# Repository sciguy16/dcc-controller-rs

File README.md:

# dcc-controller-rs
Open source lightweight DCC controller with firmware written in Rust

Based on the STM32F103C8T6 "blue pill" board - specifically the C8 version
rather than the C6 because the former has 64k of flash, and the graphics
components push the binary size up to around 51k.

## Features
* Two control potentiometers to control two locomotives, with short-mode
addresses selected via dipswitches
* Potentiometers are centre-off; rotate left to drive the corresponding
locomotive in reverse, and right to drive it forwards
* LED for each channel to show when it is active
* On-off-on mini slide switch to select programming mode
  * programming mode disables all control functions and just sends out
DCC IDLE packets until the "program" button is pressed
  * Controller will then send out the programming sequence to program the
locomotive with the address set on the selected channel
* Current measurement and overcurrent shut-off
* Overcurrent alarm LED
* Screw terminals to connect power supply and track outputs
* Pure-Rust open source firmware based on dcc-rs
* Open source hardware

## Installation
Ensure that the `thumbv7m-none-eabi` target and the `probe-run` tool have
been installed and then `cargo run --release` will automatically flash the
compiled firmware onto the device.

```bash
rustup target add thumbv7m-none-eabi
cargo install probe-run
cargo run --release
DEFMT_LOG=off cargo run --release # Disable defmt logging
```

# License
Source code for the software components is distributed under the terms
of the Mozilla Public License Version 2.0.

Design files for the hardware components are distributed under the terms
of the CERN Open Hardware Licence Version 2 - Weakly Reciprocal.

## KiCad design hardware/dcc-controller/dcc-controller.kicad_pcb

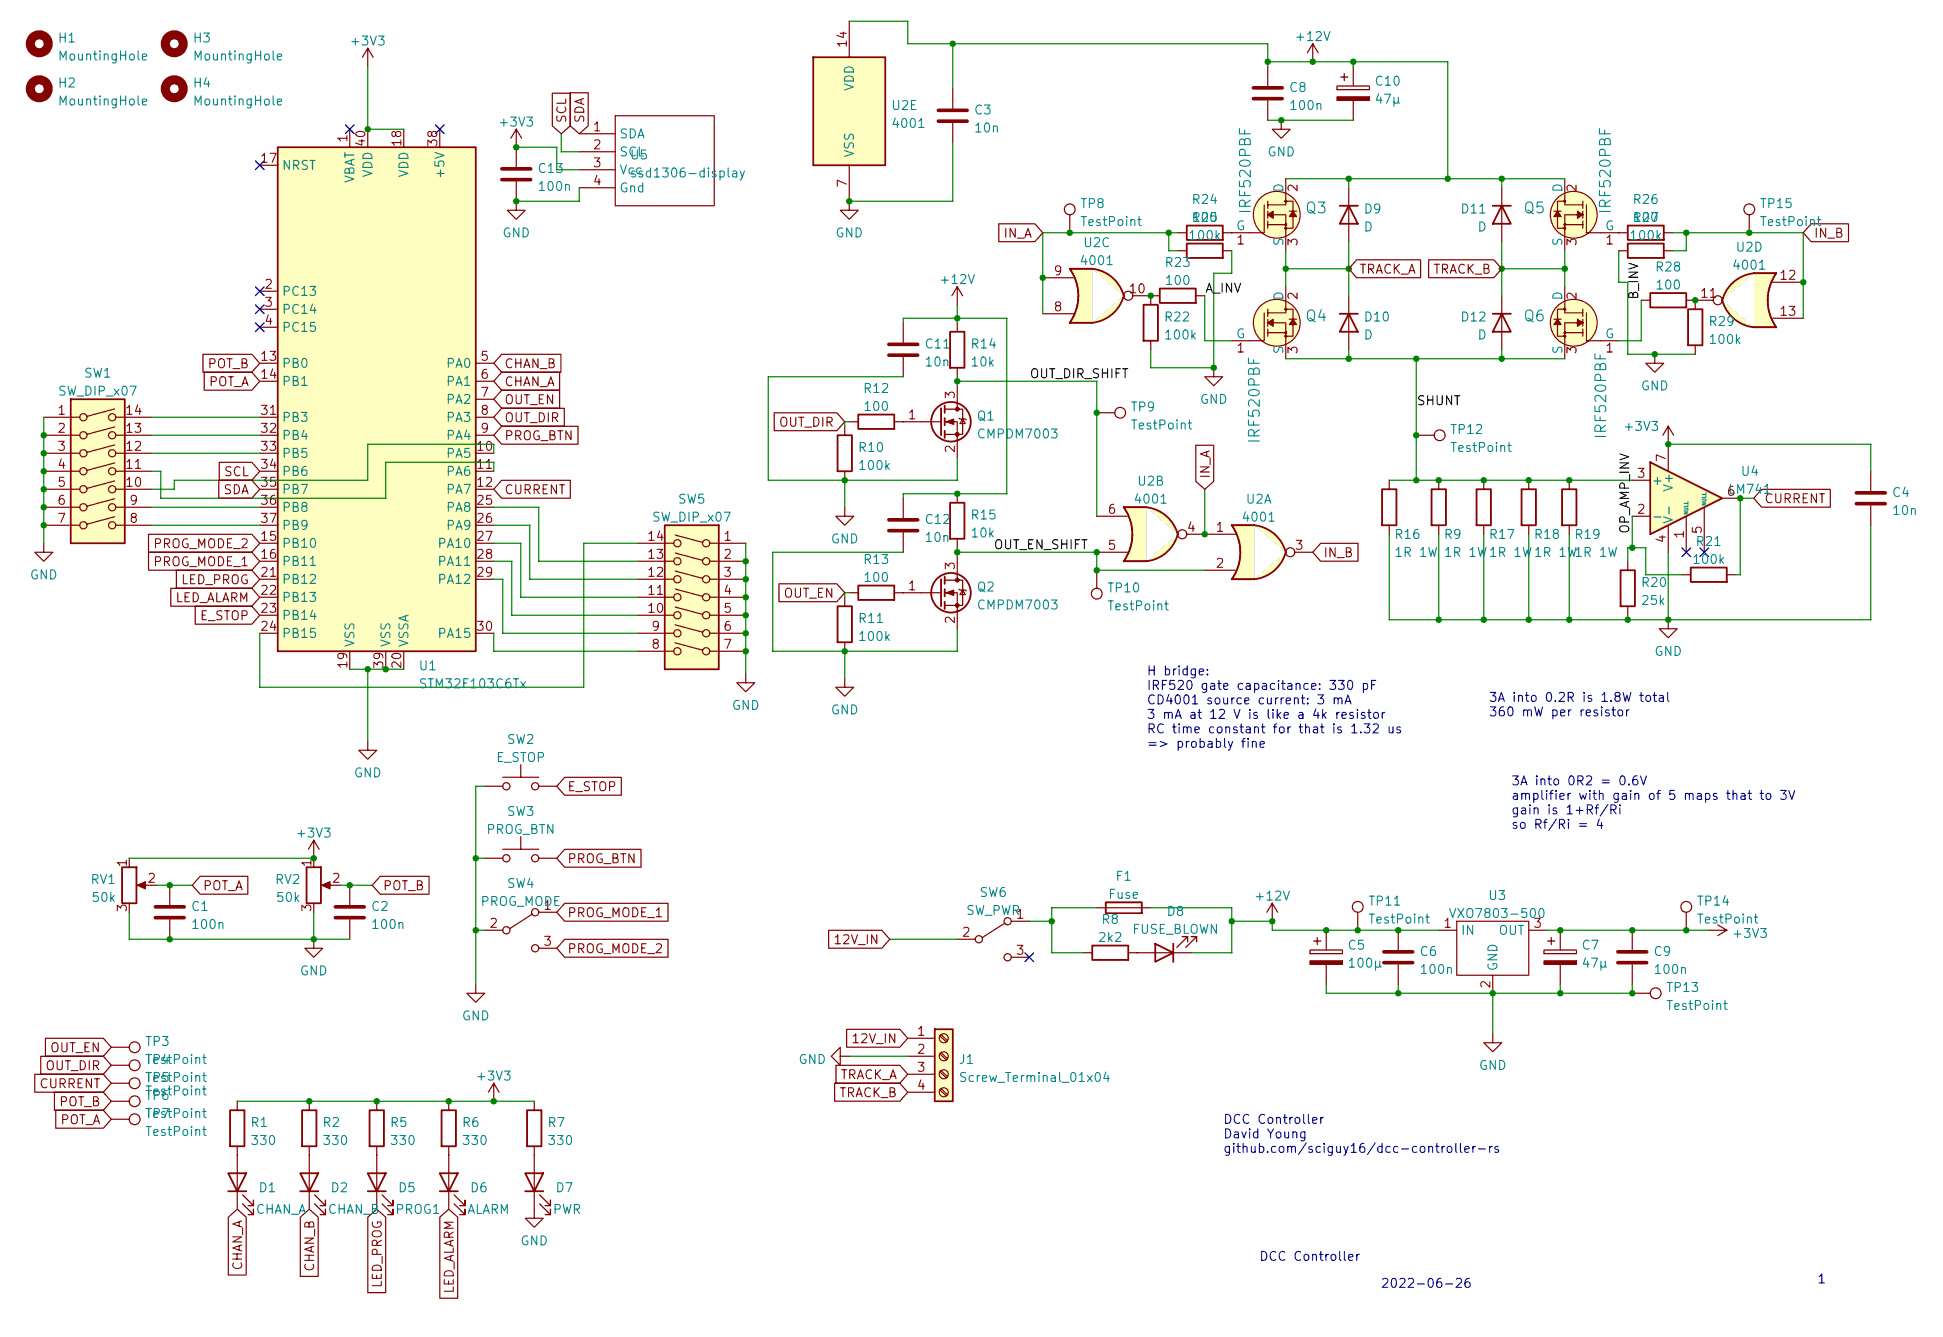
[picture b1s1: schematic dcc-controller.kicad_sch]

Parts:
C1, C2, C6, C8, C9, C13: 100n; C_0805_2012Metric
C3, C4, C11, C12: 10n; C_0805_2012Metric
C5: 100µ; CP_Radial_D5.0mm_P2.50mm
C7, C10: 47µ; CP_Radial_D5.0mm_P2.50mm
D1: CHAN_A; LED_0805_2012Metric
D2: CHAN_B; LED_0805_2012Metric
D5: PROG; LED_0805_2012Metric
D6: ALARM; LED_0805_2012Metric
D7: PWR; LED_0805_2012Metric
D8: FUSE_BLOWN; LED_0805_2012Metric
D9, D10, D11, D12: D; D_MELF
F1: Fuse; automotive-fuse-mount
H1, H2, H3, H4: MountingHole; MountingHole_3.2mm_M3
J1: Screw_Terminal_01x04; TerminalBlock_bornier-4_P5.08mm
Q1, Q2: CMPDM7003; SOT-23
Q3, Q4, Q5, Q6: IRF520PBF; TO-220F-3_Vertical; MPN IRF510PBF; Digi-Key_PN IRF510PBF-ND
R1, R2, R5, R6, R7: 330; R_0805_2012Metric
R8: 2k2; R_0805_2012Metric
R9, R16, R17, R18, R19: 1R 1W; R_Axial_DIN0207_L6.3mm_D2.5mm_P10.16mm_Horizontal
R10, R11, R21, R22, R25, R27, R29: 100k; R_0805_2012Metric
R12, R13, R23, R24, R26, R28: 100; R_0805_2012Metric
R14, R15: 10k; R_0805_2012Metric
R20: 25k; R_0805_2012Metric
RV1, RV2: 50k; Potentiometer_Bourns_PTV09A-1_Single_Vertical
SW1, SW5: SW_DIP_x07; DIP-14_W7.62mm_Socket
SW2: E_STOP; SW_PUSH_6mm_H5mm
SW3: PROG_BTN; SW_PUSH_6mm_H5mm
SW4: PROG_MODE; dp3t
SW6: SW_PWR; spdt-slide-switch
TP3, TP4, TP5, TP6, TP7, TP8, TP9, TP10, TP11, TP12, TP13, TP14, TP15: TestPoint; TestPoint_THTPad_D2.0mm_Drill1.0mm
U1: STM32F103C6Tx; stm32-blue-pill
U2: 4001; SOIC-14_3.9x8.7mm_P1.27mm
U3: VXO7803-500; TO-220-3_Vertical
U4: LM741; DIP-8_W7.62mm
U5: ssd1306-display

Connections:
12V_IN: J1.1, SW6.2 (B)
+3V3: C4.2, C7.1, C9.1, C13.1, R1.1, R2.1, R5.1, R6.1, R7.1, RV1.1, RV2.1, TP14.1, U1.18 (VDD), U1.40 (VDD), U3.3 (OUT), U4.7 (V+), U5.3 (Vcc)
+12V: C3.1, C5.1, C6.1, C8.2, C10.1, C11.1, C12.1, D8.1 (K), D9.1 (K), D11.1 (K), F1.2, Q3.2 (D), Q5.2 (D), R14.1, R15.1, TP11.1, U2.14 (VDD), U3.1 (IN)
/A_INV: Q4.1 (G), R23.2
/B_INV: Q6.1 (G), R28.1
/OP_AMP_INV: R20.1, R21.1, U4.2 (-)
/OUT_DIR_SHIFT: Q1.3 (D), R14.2, TP9.1, U2.6
/OUT_EN_SHIFT: Q2.3 (D), R15.2, TP10.1, U2.2, U2.5
/SHUNT: D10.2 (A), D12.2 (A), Q4.3 (S), Q6.3 (S), R9.1, R16.1, R17.1, R18.1, R19.1, TP12.1, U4.3 (+)
CHAN_A: D1.1 (K), U1.6 (PA1)
CHAN_B: D2.1 (K), U1.5 (PA0)
CURRENT: R21.2, TP5.1, U1.12 (PA7), U4.6
E_STOP: SW2.2, U1.23 (PB14)
GND: C1.2, C2.2, C3.2, C4.1, C5.2, C6.2, C7.2, C8.1, C9.2, C10.2, C11.2, C12.2, C13.2, D7.1 (K), J1.2, Q1.2 (S), Q2.2 (S), R9.2, R10.2, R11.2, R16.2, R17.2, R18.2, R19.2, R20.2, R22.2, R25.2, R27.1, R29.2, RV1.3, RV2.3, SW1.1, SW1.2, SW1.3, SW1.4, SW1.5, SW1.6, SW1.7, SW2.1, SW3.1, SW4.2 (B), SW5.1, SW5.2, SW5.3, SW5.4, SW5.5, SW5.6, SW5.7, TP13.1, U1.19 (VSS), U1.20 (VSSA), U1.39 (VSS), U2.7 (VSS), U3.2 (GND), U4.4 (V-), U5.4 (Gnd)
IN_A: R24.1, R25.1, TP8.1, U2.1, U2.4, U2.8, U2.9
IN_B: R26.2, R27.2, TP15.1, U2.3, U2.12, U2.13
LED_ALARM: D6.1 (K), U1.22 (PB13)
LED_PROG: D5.1 (K), U1.21 (PB12)
unnamed: D1.2 (A), R1.2
unnamed: D2.2 (A), R2.2
unnamed: D5.2 (A), R5.2
unnamed: D6.2 (A), R6.2
unnamed: D7.2 (A), R7.2
unnamed: D8.2 (A), R8.2
unnamed: F1.1, R8.1, SW6.1 (A)
unnamed: Q1.1 (G), R12.2
unnamed: Q2.1 (G), R13.2
unnamed: Q3.1 (G), R24.2
unnamed: Q5.1 (G), R26.1
unnamed: R22.1, R23.1, U2.10
unnamed: R28.2, R29.1, U2.11
unnamed: SW1.8, U1.37 (PB9)
unnamed: SW1.9, U1.36 (PB8)
unnamed: SW1.10, U1.10 (PA5)
unnamed: SW1.11, U1.11 (PA6)
unnamed: SW1.12, U1.33 (PB5)
unnamed: SW1.13, U1.32 (PB4)
unnamed: SW1.14, U1.31 (PB3)
unnamed: SW5.8, U1.30 (PA15)
unnamed: SW5.9, U1.29 (PA12)
unnamed: SW5.10, U1.28 (PA11)
unnamed: SW5.11, U1.27 (PA10)
unnamed: SW5.12, U1.26 (PA9)
unnamed: SW5.13, U1.25 (PA8)
unnamed: SW5.14, U1.24 (PB15)
OUT_DIR: R10.1, R12.1, TP4.1, U1.8 (PA3)
OUT_EN: R11.1, R13.1, TP3.1, U1.7 (PA2)
POT_A: C1.1, RV1.2, TP7.1, U1.14 (PB1)
POT_B: C2.1, RV2.2, TP6.1, U1.13 (PB0)
PROG_BTN: SW3.2, U1.9 (PA4)
PROG_MODE_1: SW4.1 (A), U1.16 (PB11)
PROG_MODE_2: SW4.3 (C), U1.15 (PB10)
SCL: U1.34 (PB6), U5.2 (SCL)
SDA: U1.35 (PB7), U5.1 (SDA)
TRACK_A: D9.2 (A), D10.1 (K), J1.3, Q3.3 (S), Q4.2 (D)
TRACK_B: D11.2 (A), D12.1 (K), J1.4, Q5.3 (S), Q6.2 (D)

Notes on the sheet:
DCC Controller
H bridge: IRF520 gate capacitance: 330 pF CD4001 source current: 3 mA 3 mA at 12 V is like a 4k resistor RC time constant for that is 1.32 us => probably fine
DCC Controller David Young github.com/sciguy16/dcc-controller-rs
2022-06-26
3A into 0.2R is 1.8W total 360 mW per resistor
3A into 0R2 = 0.6V amplifier with gain of 5 maps that to 3V gain is 1+Rf/Ri so Rf/Ri = 4

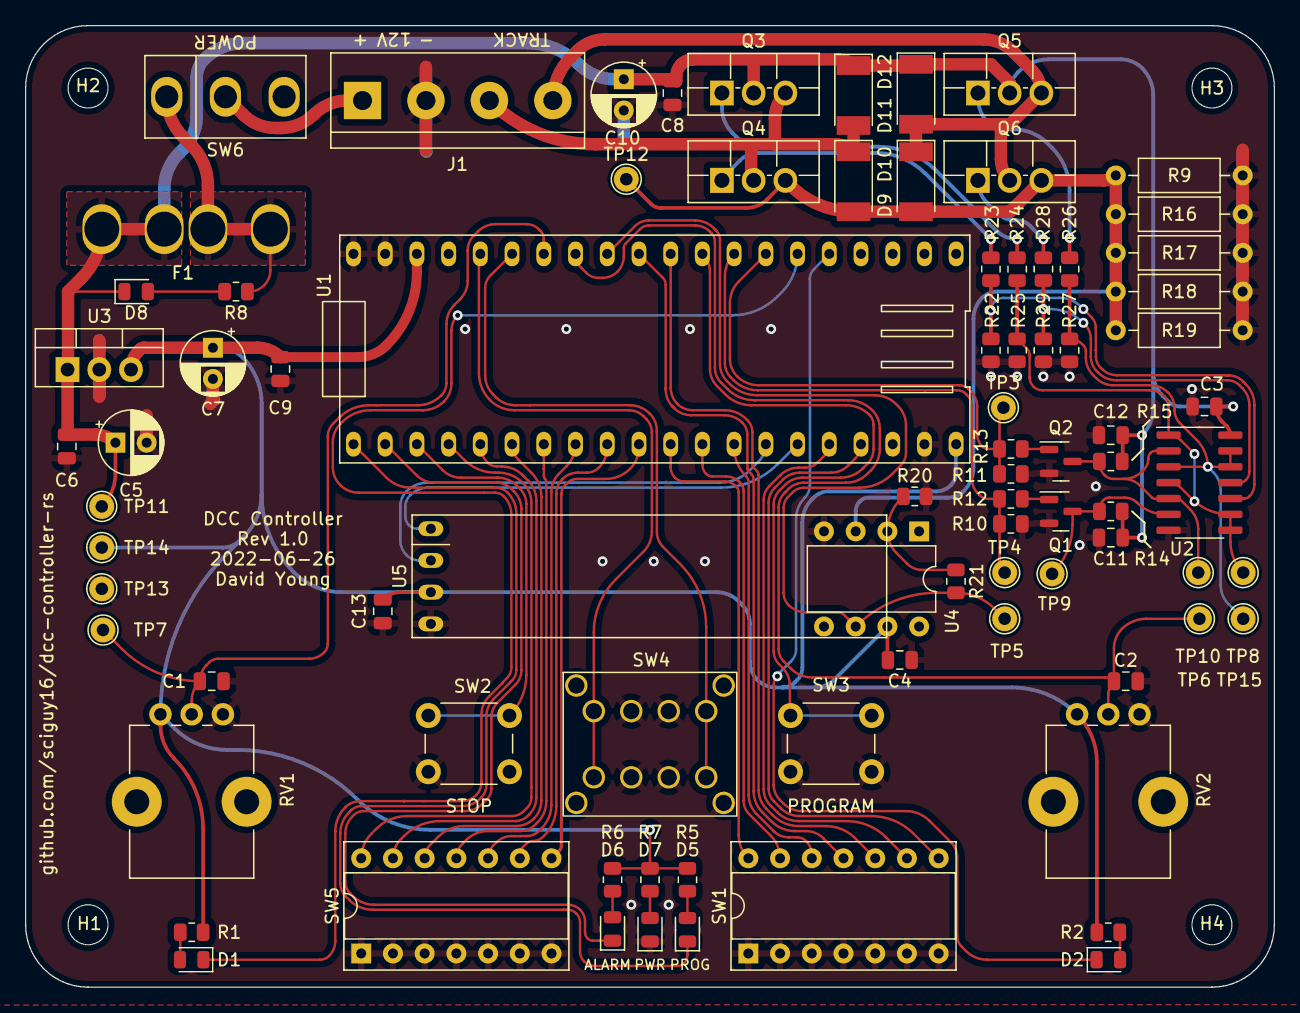
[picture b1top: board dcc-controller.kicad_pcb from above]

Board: 2 copper layers, 100.0 x 77.0 mm, 88 parts (0 on the bottom side), 56 nets.

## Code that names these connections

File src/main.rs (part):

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// file, you can obtain one at https://mozilla.org/MPL/2.0/.

// Pinout:
// POT_LEFT: PB0
// POT_RIGHT: PB1
// DIPSW_LEFT: PB15, PA8, PA9, PA10, PA11, PA12, PA15
// DIPSW_RIGHT: PB3, PB4, PB5, PA6, PA5, PB8, PB9
// SCL: PB6
// SDA: PB7
// LED_LEFT: PA1
// LED_RIGHT: PA0
// LED_PROG: PB12
// LED_ALARM: PB13
// BTN_STOP: PB14
// BTN_PROG: PA4
// SW_PROG_LEFT: PB10
// SW_PROG_RIGHT: PB11
// OUT_EN: PA2
// OUT_DIR: PA3
// CURRENT_SENSE: PA7

#![no_main]
#![no_std]
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}

// A type definition for the GPIO pin to be used for our LED
type DccDirPin = gpioa::PA3<Output<PushPull>>;

// Make DCC thingy globally available
static G_DCC: Mutex<RefCell<Option<DccInterruptHandler<DccDirPin>>>> =
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static TX_BUFFER: Mutex<RefCell<Option<(SerialiseBuffer, usize)>>> =
    Mutex::new(RefCell::new(None));

type LedAlarm = gpiob::PB13<Output<PushPull>>;
static LED_ALARM: Mutex<RefCell<Option<LedAlarm>>> =
    Mutex::new(RefCell::new(None));

type EnablePin = gpioa::PA2<Output<PushPull>>;
static ENABLE_PIN: Mutex<RefCell<Option<EnablePin>>> =
    Mutex::new(RefCell::new(None));

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    let mut gpiob = dp.GPIOB.split();

    // store the alarm led pin so that it is available for the panic handler
    let mut led_alarm = gpiob.pb13.into_push_pull_output(&mut gpiob.crh);
    led_alarm.set_high();
    cortex_m::interrupt::free(|cs| {
        *LED_ALARM.borrow(cs).borrow_mut() = Some(led_alarm)
    });

    info!("Initialise DCC interrupt handler");
    let dcc_pin = gpioa.pa3.into_push_pull_output(&mut gpioa.crl);
    let dcc = DccInterruptHandler::new(dcc_pin);
    cortex_m::interrupt::free(|cs| *G_DCC.borrow(cs).borrow_mut() = Some(dcc));

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
    info!("Init I2C");
    cp.DWT.enable_cycle_counter();
    let scl = gpiob.pb6.into_alternate_open_drain(&mut gpiob.crl);
    let sda = gpiob.pb7.into_alternate_open_drain(&mut gpiob.crl);
    let i2c = BlockingI2c::i2c1(
        dp.I2C1,
        (scl, sda),
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    let mut delay = cp.SYST.delay(&clocks);

    // LED to show when power is on
    let mut led1 = gpioa.pa1.into_push_pull_output(&mut gpioa.crl);
    let mut led2 = gpioa.pa0.into_push_pull_output(&mut gpioa.crl);
    let mut led_prog = gpiob.pb12.into_push_pull_output(&mut gpiob.crh);
    led1.set_high();
    led2.set_high();
    led_prog.set_high();

    let mut out_en = gpioa.pa2.into_push_pull_output(&mut gpioa.crl);
    out_en.set_high();
    cortex_m::interrupt::free(|cs| {
        *ENABLE_PIN.borrow(cs).borrow_mut() = Some(out_en)
    });

    // remove pins from the jtag peripheral and set up pins for address
    // selectors
    info!("Set up address pins");
    let (pa15, pb3, pb4) =
        afio.mapr.disable_jtag(gpioa.pa15, gpiob.pb3, gpiob.pb4);
    let mut addr_left = AddressSwitches::new(
        gpiob.pb15.into_pull_up_input(&mut gpiob.crh),
        gpioa.pa8.into_pull_up_input(&mut gpioa.crh),
        gpioa.pa9.into_pull_up_input(&mut gpioa.crh),
        gpioa.pa10.into_pull_up_input(&mut gpioa.crh),
        gpioa.pa11.into_pull_up_input(&mut gpioa.crh),
        gpioa.pa12.into_pull_up_input(&mut gpioa.crh),
        pa15.into_pull_up_input(&mut gpioa.crh),
    );
    let mut addr_right = AddressSwitches::new(
        pb3.into_pull_up_input(&mut gpiob.crl),
        pb4.into_pull_up_input(&mut gpiob.crl),
        gpiob.pb5.into_pull_up_input(&mut gpiob.crl),
        gpioa.pa6.into_pull_up_input(&mut gpioa.crl),
        gpioa.pa5.into_pull_up_input(&mut gpioa.crl),
        gpiob.pb8.into_pull_up_input(&mut gpiob.crh),
        gpiob.pb9.into_pull_up_input(&mut gpiob.crh),
    );
    info!(
        "addresses: left={}, right={}",
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    );

    info!("Configure button pins");
    let btn_stop = gpiob.pb14.into_pull_up_input(&mut gpiob.crh);
    let btn_prog = gpioa.pa4.into_pull_up_input(&mut gpioa.crl);
    let sw_prog_left = gpiob.pb11.into_pull_up_input(&mut gpiob.crh);
    let sw_prog_right = gpiob.pb10.into_pull_up_input(&mut gpiob.crh);

    // set up ADC
    info!("Configure ADC");
    let mut adc1 = adc::Adc::adc1(dp.ADC1, clocks);
    let mut ch0 = gpiob.pb1.into_analog(&mut gpiob.crl);
    let mut ch1 = gpiob.pb0.into_analog(&mut gpiob.crl);

    let mut adc2 = adc::Adc::adc2(dp.ADC2, clocks);
    let mut current_pin = gpioa.pa7.into_analog(&mut gpioa.crl);

    let mut chan_left = ChannelProps::with_address(addr_left.value());
    let mut chan_right = ChannelProps::with_address(addr_right.value());
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    info!("Enter main loop");
    loop {
        // read the current
        let current: u16 = adc2.read(&mut current_pin).unwrap();

        // update address
        addr_left.update();
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
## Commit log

2022-06-15 Create Rust template and licences
2022-06-15 List specifications and make empty kicad project
2022-06-16 Implement two-channel DCC controller
2022-06-18 Make schematic for controller
2022-06-19 Inital layout
2022-06-24 Implement display functions and upgrade to STM32F103C8T6
2022-06-24 Update schematic for display
2022-06-25 Do layout and routing for new display version
2022-06-26 Tidy up routing
2022-06-26 Tidy up silkscreen
2022-06-26 Add gerbers and printouts
2022-07-13 Update pin mappings for pcb
2022-07-14 Implement address selector for left control
2022-07-14 Turn on alarm LED when panic
2022-07-14 Make logging less verbose
2022-07-14 Implement the address switches for the right channel
2022-07-14 Implement UI state machine
2022-07-15 Refactor address switch into module and make alarm light blink on panic
2022-07-15 Refactor channel properties into a struct
2022-07-15 Factor direction arrow into a method on ChannelProps
2022-07-15 Remove redundant code
2022-07-16 Update documentation
2022-07-16 Add description of STM32
2022-07-16 Update dependencies
2022-07-16 Installation instructions
2023-02-14 Bump cortex-m-rt from 0.7.1 to 0.7.3
    Bumps [cortex-m-rt](https://github.com/rust-embedded/cortex-m) from 0.7.1 to 0.7.3.
    - [Release notes](https://github.com/rust-embedded/cortex-m/releases)
    - [Changelog](https://github.com/rust-embedded/cortex-m/blob/master/CHANGELOG.md)
    - [Commits](https://github.com/rust-embedded/cortex-m/compare/v0.7.1...v0.7.3)
    ---
    updated-dependencies:
